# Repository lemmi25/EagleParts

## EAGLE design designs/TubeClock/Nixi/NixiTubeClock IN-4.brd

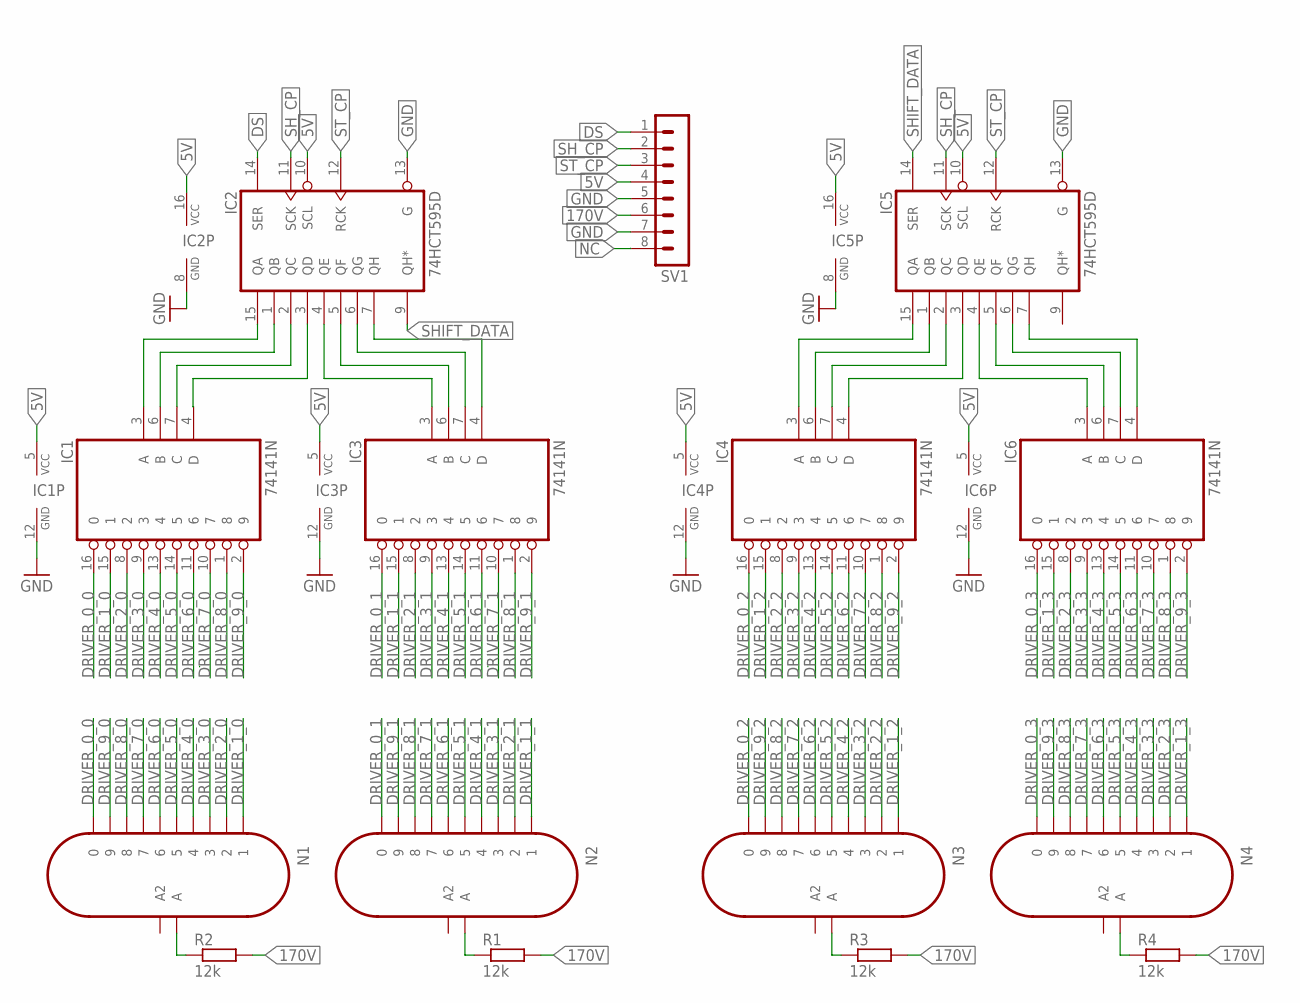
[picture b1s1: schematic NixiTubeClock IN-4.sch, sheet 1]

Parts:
IC1, IC3, IC4, IC6: 74141N; DIL16
IC2, IC5: 74HCT595D; SO16
N1, N2, N3, N4: IN-4; IN-18
R1, R2, R3, R4: 12k; R1206
SV1: MA08-1

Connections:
5V: IC1.5 (VCC), IC2.10 (SCL), IC2.16 (VCC), IC3.5 (VCC), IC4.5 (VCC), IC5.10 (SCL), IC5.16 (VCC), IC6.5 (VCC), SV1.4
170V: R1.2, R2.2, R3.2, R4.2, SV1.6
DRIVER_0_0: IC1.16 (0), N1.N/C2 (0)
DRIVER_0_1: IC3.16 (0), N2.N/C2 (0)
DRIVER_0_2: IC4.16 (0), N3.N/C2 (0)
DRIVER_0_3: IC6.16 (0), N4.N/C2 (0)
DRIVER_1_0: IC1.15 (1), N1.9 (1)
DRIVER_1_1: IC3.15 (1), N2.9 (1)
DRIVER_1_2: IC4.15 (1), N3.9 (1)
DRIVER_1_3: IC6.15 (1), N4.9 (1)
DRIVER_2_0: IC1.8 (2), N1.8 (2)
DRIVER_2_1: IC3.8 (2), N2.8 (2)
DRIVER_2_2: IC4.8 (2), N3.8 (2)
DRIVER_2_3: IC6.8 (2), N4.8 (2)
DRIVER_3_0: IC1.9 (3), N1.1 (3)
DRIVER_3_1: IC3.9 (3), N2.1 (3)
DRIVER_3_2: IC4.9 (3), N3.1 (3)
DRIVER_3_3: IC6.9 (3), N4.1 (3)
DRIVER_4_0: IC1.13 (4), N1.N/C (4)
DRIVER_4_1: IC3.13 (4), N2.N/C (4)
DRIVER_4_2: IC4.13 (4), N3.N/C (4)
DRIVER_4_3: IC6.13 (4), N4.N/C (4)
DRIVER_5_0: IC1.14 (5), N1.A2 (5)
DRIVER_5_1: IC3.14 (5), N2.A2 (5)
DRIVER_5_2: IC4.14 (5), N3.A2 (5)
DRIVER_5_3: IC6.14 (5), N4.A2 (5)
DRIVER_6_0: IC1.11 (6), N1.4 (6)
DRIVER_6_1: IC3.11 (6), N2.4 (6)
DRIVER_6_2: IC4.11 (6), N3.4 (6)
DRIVER_6_3: IC6.11 (6), N4.4 (6)
DRIVER_7_0: IC1.10 (7), N1.7
DRIVER_7_1: IC3.10 (7), N2.7
DRIVER_7_2: IC4.10 (7), N3.7
DRIVER_7_3: IC6.10 (7), N4.7
DRIVER_8_0: IC1.1 (8), N1.5 (8)
DRIVER_8_1: IC3.1 (8), N2.5 (8)
DRIVER_8_2: IC4.1 (8), N3.5 (8)
DRIVER_8_3: IC6.1 (8), N4.5 (8)
DRIVER_9_0: IC1.2 (9), N1.6 (9)
DRIVER_9_1: IC3.2 (9), N2.6 (9)
DRIVER_9_2: IC4.2 (9), N3.6 (9)
DRIVER_9_3: IC6.2 (9), N4.6 (9)
DS: IC2.14 (SER), SV1.1
GND: IC1.12 (GND), IC2.8 (GND), IC2.13 (G), IC3.12 (GND), IC4.12 (GND), IC5.8 (GND), IC5.13 (G), IC6.12 (GND), SV1.5, SV1.7
unnamed: IC4.4 (D), IC5.3 (QD)
unnamed: N2.0 (A), R1.1
unnamed: N3.0 (A), R3.1
unnamed: N4.0 (A), R4.1
unnamed: N1.0 (A), R2.1
unnamed: IC1.3 (A), IC2.15 (QA)
unnamed: IC1.6 (B), IC2.1 (QB)
unnamed: IC1.7 (C), IC2.2 (QC)
unnamed: IC1.4 (D), IC2.3 (QD)
unnamed: IC2.4 (QE), IC3.3 (A)
unnamed: IC2.5 (QF), IC3.6 (B)
unnamed: IC2.6 (QG), IC3.7 (C)
unnamed: IC2.7 (QH), IC3.4 (D)
unnamed: IC4.3 (A), IC5.15 (QA)
unnamed: IC4.6 (B), IC5.1 (QB)
unnamed: IC4.7 (C), IC5.2 (QC)
unnamed: IC5.4 (QE), IC6.3 (A)
unnamed: IC5.5 (QF), IC6.6 (B)
unnamed: IC5.6 (QG), IC6.7 (C)
unnamed: IC5.7 (QH), IC6.4 (D)
NC: SV1.8
SHIFT_DATA: IC2.9 (QH*), IC5.14 (SER)
SH_CP: IC2.11 (SCK), IC5.11 (SCK), SV1.2
ST_CP: IC2.12 (RCK), IC5.12 (RCK), SV1.3

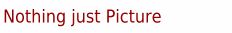
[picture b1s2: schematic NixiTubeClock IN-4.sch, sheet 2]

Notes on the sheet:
Nothing just Picture

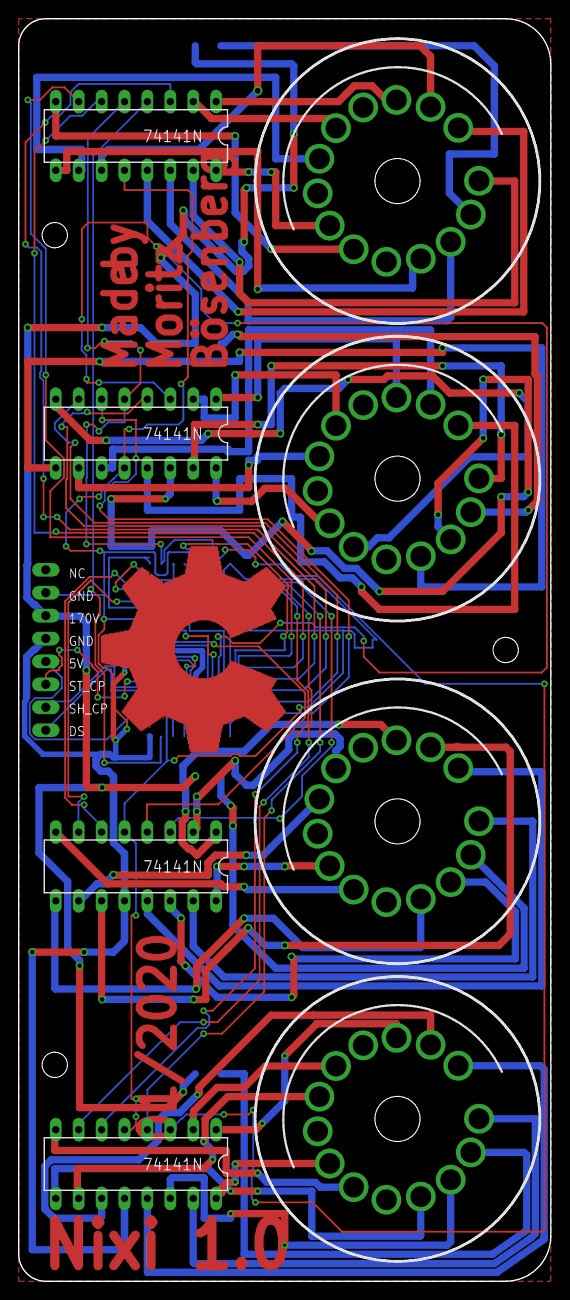
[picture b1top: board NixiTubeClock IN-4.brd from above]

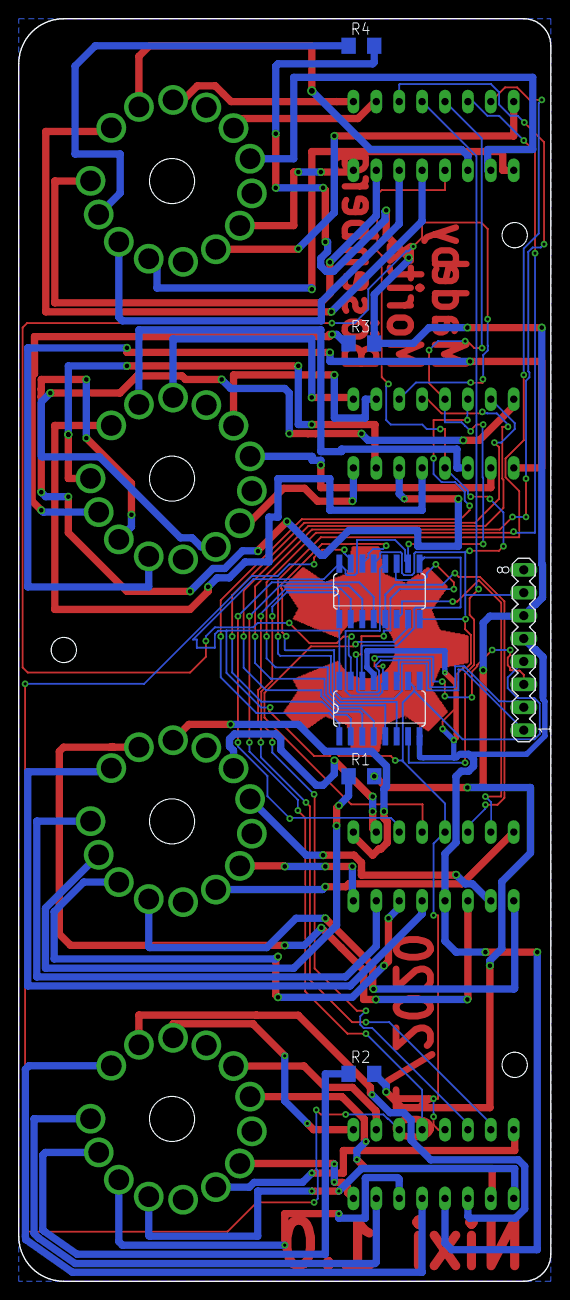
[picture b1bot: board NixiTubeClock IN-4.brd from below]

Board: 2 copper layers, 59.0 x 140.0 mm, 15 parts (7 on the bottom side), 67 nets.

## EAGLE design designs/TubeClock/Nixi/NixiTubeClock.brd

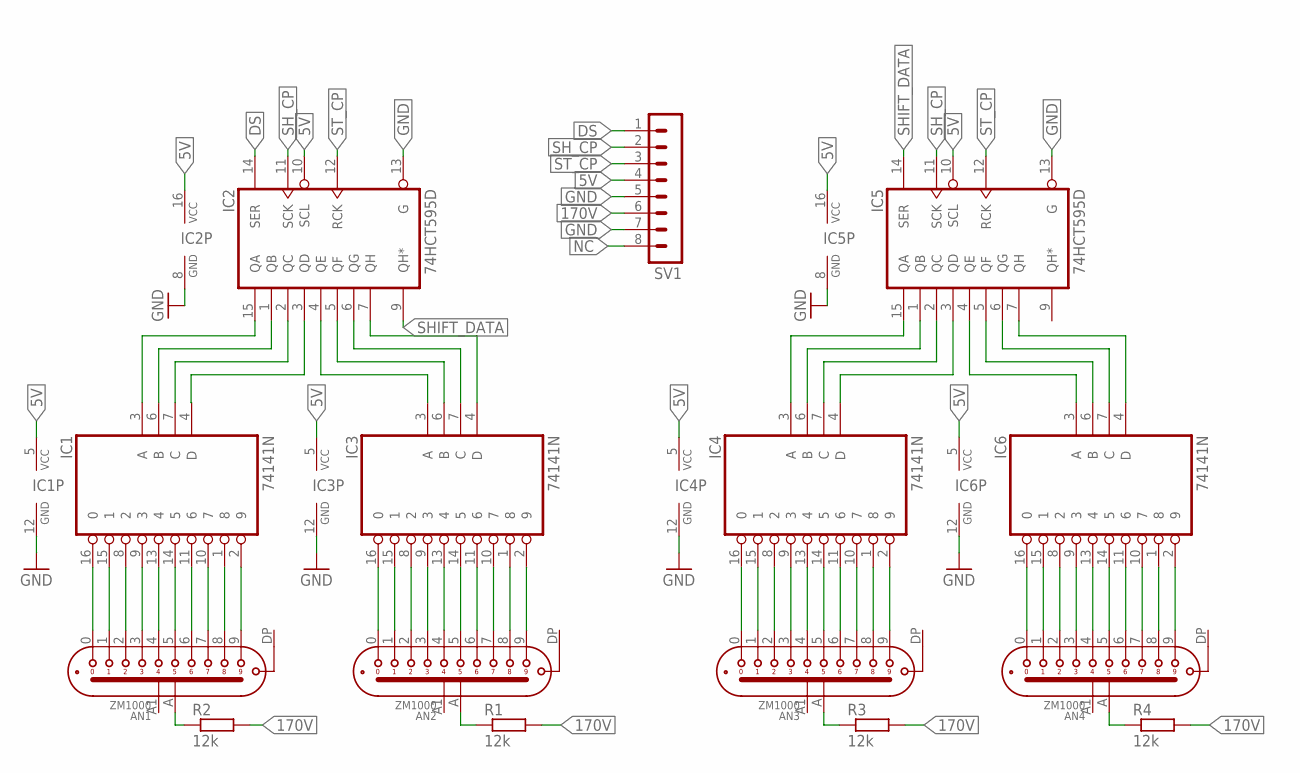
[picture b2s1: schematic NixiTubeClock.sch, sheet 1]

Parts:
AN1, AN2, AN3, AN4: ZM1000
IC1, IC3, IC4, IC6: 74141N; DIL16
IC2, IC5: 74HCT595D; SO16
R1, R2, R3, R4: 12k; R1206
SV1: MA08-1

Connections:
5V: IC1.5 (VCC), IC2.10 (SCL), IC2.16 (VCC), IC3.5 (VCC), IC4.5 (VCC), IC5.10 (SCL), IC5.16 (VCC), IC6.5 (VCC), SV1.4
170V: R1.2, R2.2, R3.2, R4.2, SV1.6
DS: IC2.14 (SER), SV1.1
GND: IC1.12 (GND), IC2.8 (GND), IC2.13 (G), IC3.12 (GND), IC4.12 (GND), IC5.8 (GND), IC5.13 (G), IC6.12 (GND), SV1.5, SV1.7
unnamed: IC4.4 (D), IC5.3 (QD)
unnamed: AN1.0, IC1.16 (0)
unnamed: AN1.1, IC1.15 (1)
unnamed: AN1.2, IC1.8 (2)
unnamed: AN1.3, IC1.9 (3)
unnamed: AN1.4, IC1.13 (4)
unnamed: AN1.5, IC1.14 (5)
unnamed: AN1.6, IC1.11 (6)
unnamed: AN1.7, IC1.10 (7)
unnamed: AN1.8, IC1.1 (8)
unnamed: AN1.9, IC1.2 (9)
unnamed: AN2.0, IC3.16 (0)
unnamed: AN2.1, IC3.15 (1)
unnamed: AN2.2, IC3.8 (2)
unnamed: AN2.3, IC3.9 (3)
unnamed: AN2.4, IC3.13 (4)
unnamed: AN2.5, IC3.14 (5)
unnamed: AN2.6, IC3.11 (6)
unnamed: AN2.7, IC3.10 (7)
unnamed: AN2.8, IC3.1 (8)
unnamed: AN2.9, IC3.2 (9)
unnamed: AN3.0, IC4.16 (0)
unnamed: AN3.1, IC4.15 (1)
unnamed: AN3.2, IC4.8 (2)
unnamed: AN3.3, IC4.9 (3)
unnamed: AN3.4, IC4.13 (4)
unnamed: AN3.5, IC4.14 (5)
unnamed: AN3.6, IC4.11 (6)
unnamed: AN3.7, IC4.10 (7)
unnamed: AN3.8, IC4.1 (8)
unnamed: AN3.9, IC4.2 (9)
unnamed: AN4.0, IC6.16 (0)
unnamed: AN4.1, IC6.15 (1)
unnamed: AN4.2, IC6.8 (2)
unnamed: AN4.3, IC6.9 (3)
unnamed: AN4.4, IC6.13 (4)
unnamed: AN4.5, IC6.14 (5)
unnamed: AN4.6, IC6.11 (6)
unnamed: AN4.7, IC6.10 (7)
unnamed: AN4.8, IC6.1 (8)
unnamed: AN4.9, IC6.2 (9)
unnamed: AN1.A (A1), R2.1
unnamed: AN2.A (A1), R1.1
unnamed: AN3.A (A1), R3.1
unnamed: AN4.A (A1), R4.1
unnamed: IC1.3 (A), IC2.15 (QA)
unnamed: IC1.6 (B), IC2.1 (QB)
unnamed: IC1.7 (C), IC2.2 (QC)
unnamed: IC1.4 (D), IC2.3 (QD)
unnamed: IC2.4 (QE), IC3.3 (A)
unnamed: IC2.5 (QF), IC3.6 (B)
unnamed: IC2.6 (QG), IC3.7 (C)
unnamed: IC2.7 (QH), IC3.4 (D)
unnamed: IC4.3 (A), IC5.15 (QA)
unnamed: IC4.6 (B), IC5.1 (QB)
unnamed: IC4.7 (C), IC5.2 (QC)
unnamed: IC5.4 (QE), IC6.3 (A)
unnamed: IC5.5 (QF), IC6.6 (B)
unnamed: IC5.6 (QG), IC6.7 (C)
unnamed: IC5.7 (QH), IC6.4 (D)
NC: SV1.8
SHIFT_DATA: IC2.9 (QH*), IC5.14 (SER)
SH_CP: IC2.11 (SCK), IC5.11 (SCK), SV1.2
ST_CP: IC2.12 (RCK), IC5.12 (RCK), SV1.3

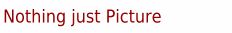
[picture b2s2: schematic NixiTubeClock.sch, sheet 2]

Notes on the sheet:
Nothing just Picture

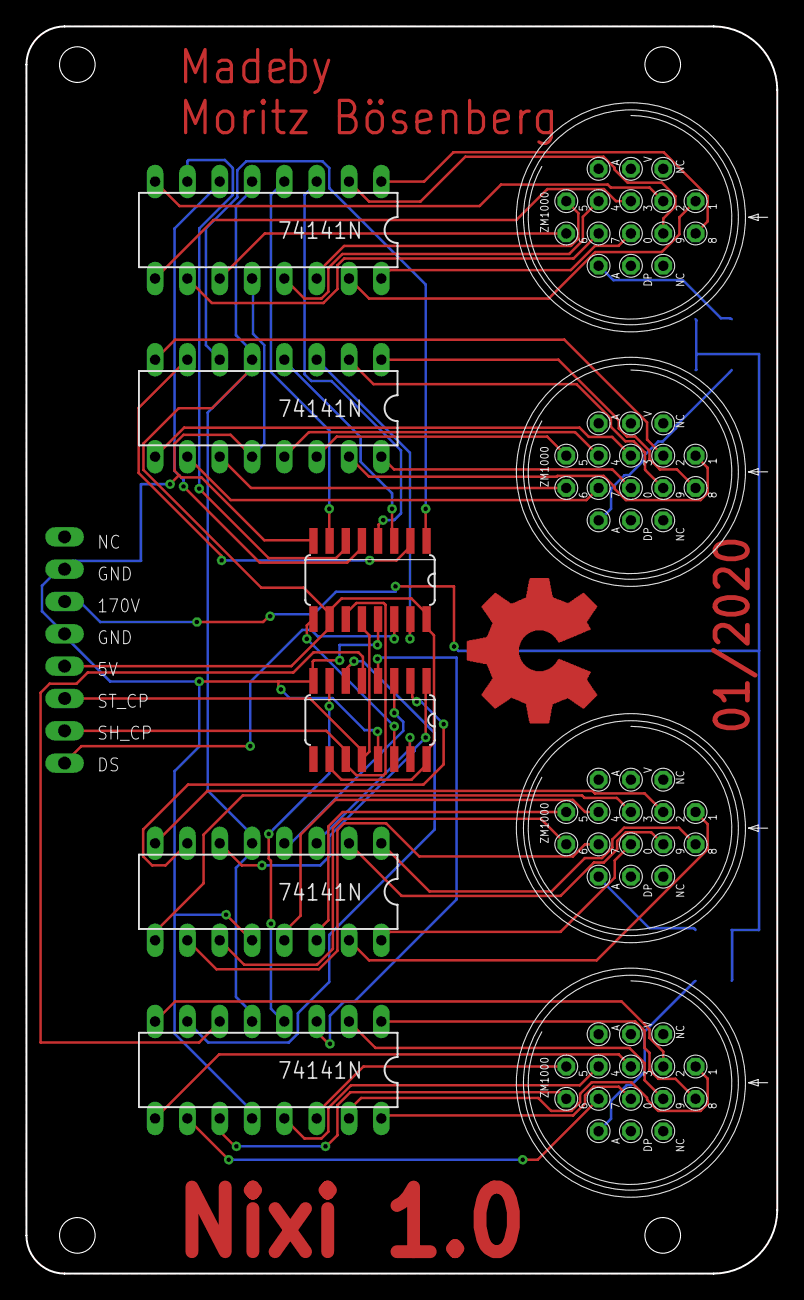
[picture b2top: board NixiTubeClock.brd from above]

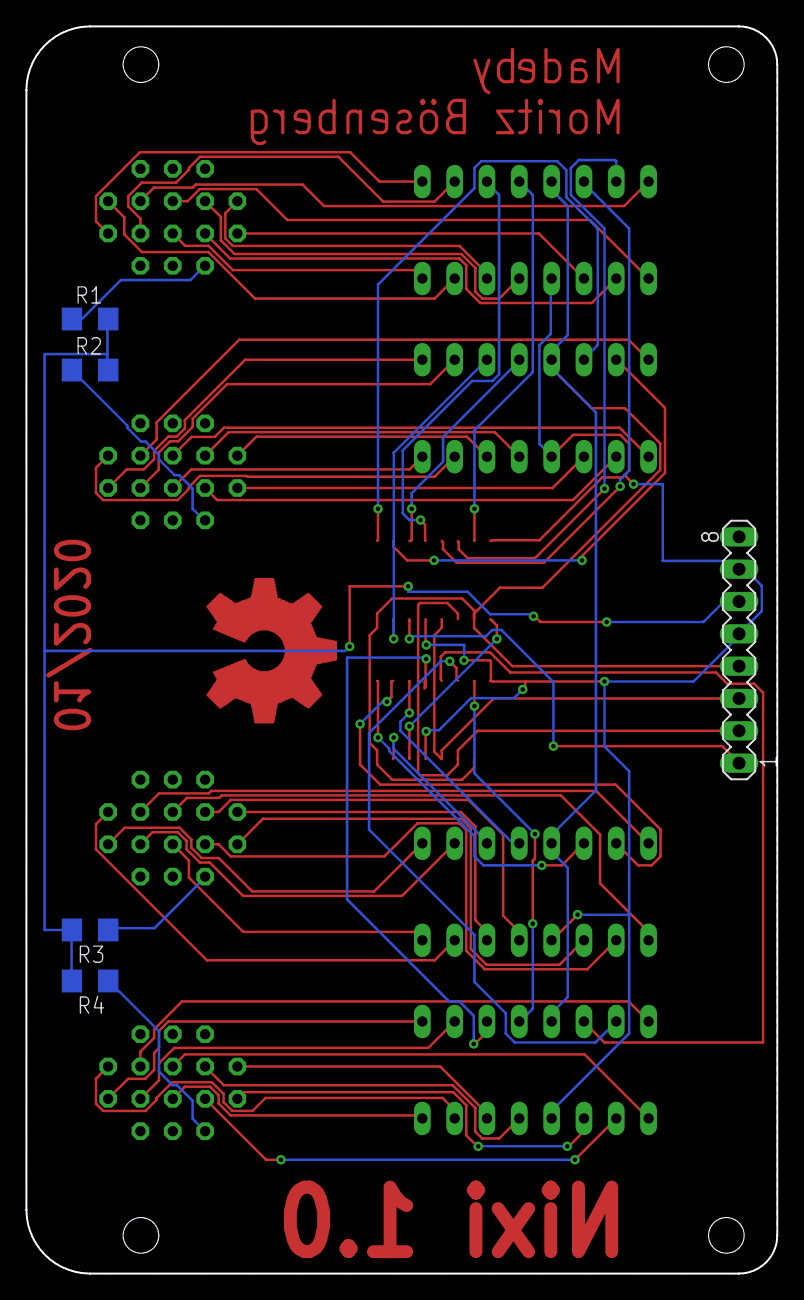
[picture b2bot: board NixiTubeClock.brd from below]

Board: 2 copper layers, 59.0 x 98.0 mm, 15 parts (5 on the bottom side), 67 nets.

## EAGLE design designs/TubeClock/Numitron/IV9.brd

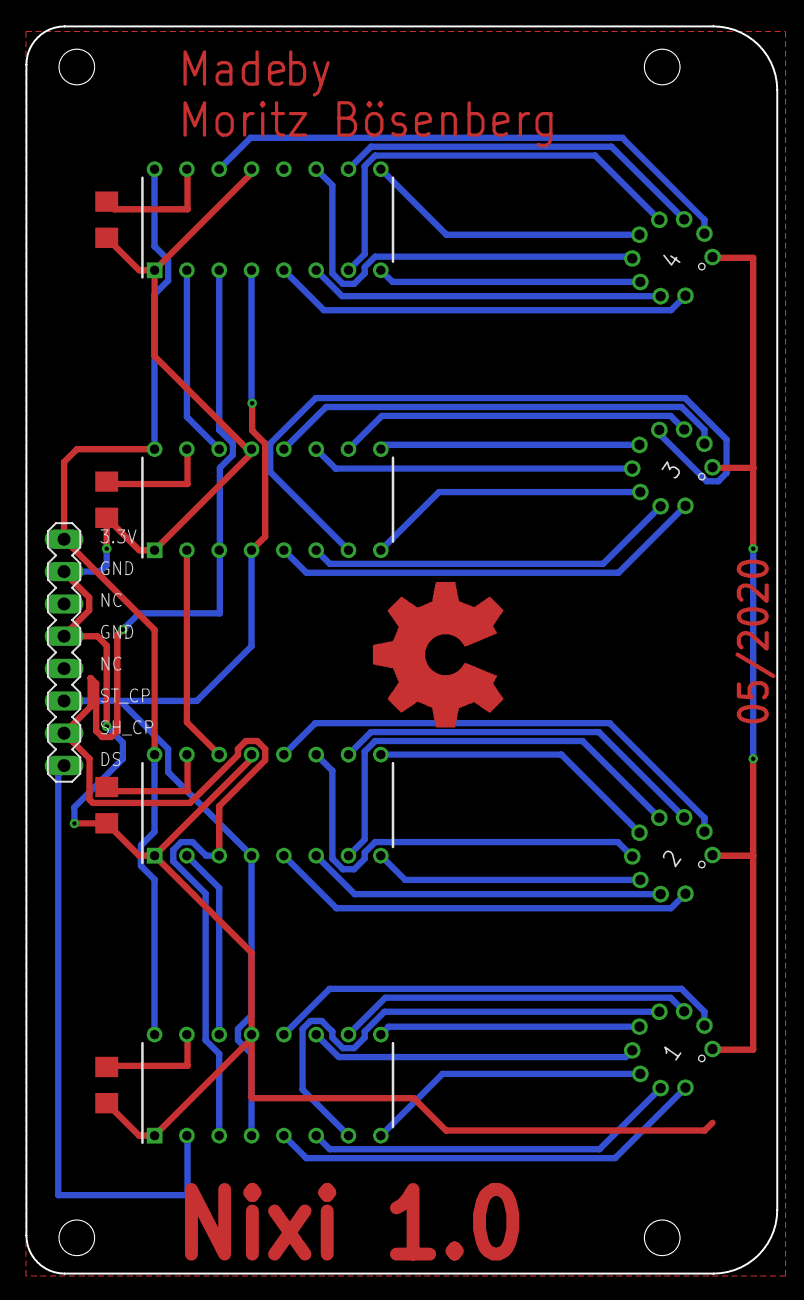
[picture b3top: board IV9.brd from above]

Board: 2 copper layers, 59.0 x 98.0 mm, 13 parts (0 on the bottom side), 44 nets.

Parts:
1, 2, 3, 4: IV-9
IC1, IC2, IC3, IC4: TLC5916IN; DIP794W53P254L1930H508Q16N
R1, R2, R3, R4: 1K; R1206
SV2: MA08-1

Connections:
3.3V: 1.1, 2.1, 3.1, 4.1, IC1.16, IC2.16, IC3.16, IC4.16, SV2.8
A_1: 1.5, IC1.9
A_2: 2.5, IC2.9
A_3: 3.5, IC3.9
A_4: 4.5, IC4.9
B_1: 1.3, IC1.10
B_2: 2.3, IC2.10
B_3: 3.3, IC3.10
B_4: 4.3, IC4.10
C_1: 1.4, IC1.7
C_2: 2.4, IC2.7
C_3: 3.4, IC3.7
C_4: 4.4, IC4.7
DEC_1: 1.2, IC1.12
DEC_2: 2.2, IC2.12
DEC_3: 3.2, IC3.12
DEC_4: 4.2, IC4.14
DS: IC1.2, SV2.1
D_1: 1.8, IC1.6
D_2: 2.8, IC2.6
D_3: 3.8, IC3.6
D_4: 4.8, IC4.6
E_1: 1.9, IC1.5
E_2: 2.9, IC2.5
E_3: 3.9, IC3.5
E_4: 4.9, IC4.5
F_1: 1.6, IC1.11
F_2: 2.6, IC2.11
F_3: 3.6, IC3.11
F_4: 4.6, IC4.11
GND: IC1.1, IC1.13, IC2.1, IC2.13, IC3.1, IC3.13, IC4.1, IC4.13, R1.1, R2.1, R3.1, R4.1, SV2.5, SV2.7
G_1: 1.7, IC1.8
G_2: 2.7, IC2.8
G_3: 3.7, IC3.8
G_4: 4.7, IC4.8
unnamed: IC1.14, IC2.2
unnamed: IC2.14, IC3.2
unnamed: IC3.14, IC4.2
R-EXT1: IC1.15, R1.2
R-EXT2: IC2.15, R2.2
R-EXT3: IC3.15, R3.2
R-EXT4: IC4.15, R4.2
SH_CP: IC1.3, IC2.3, IC3.3, IC4.3, SV2.2
ST_CP: IC1.4, IC2.4, IC3.4, IC4.4, SV2.3

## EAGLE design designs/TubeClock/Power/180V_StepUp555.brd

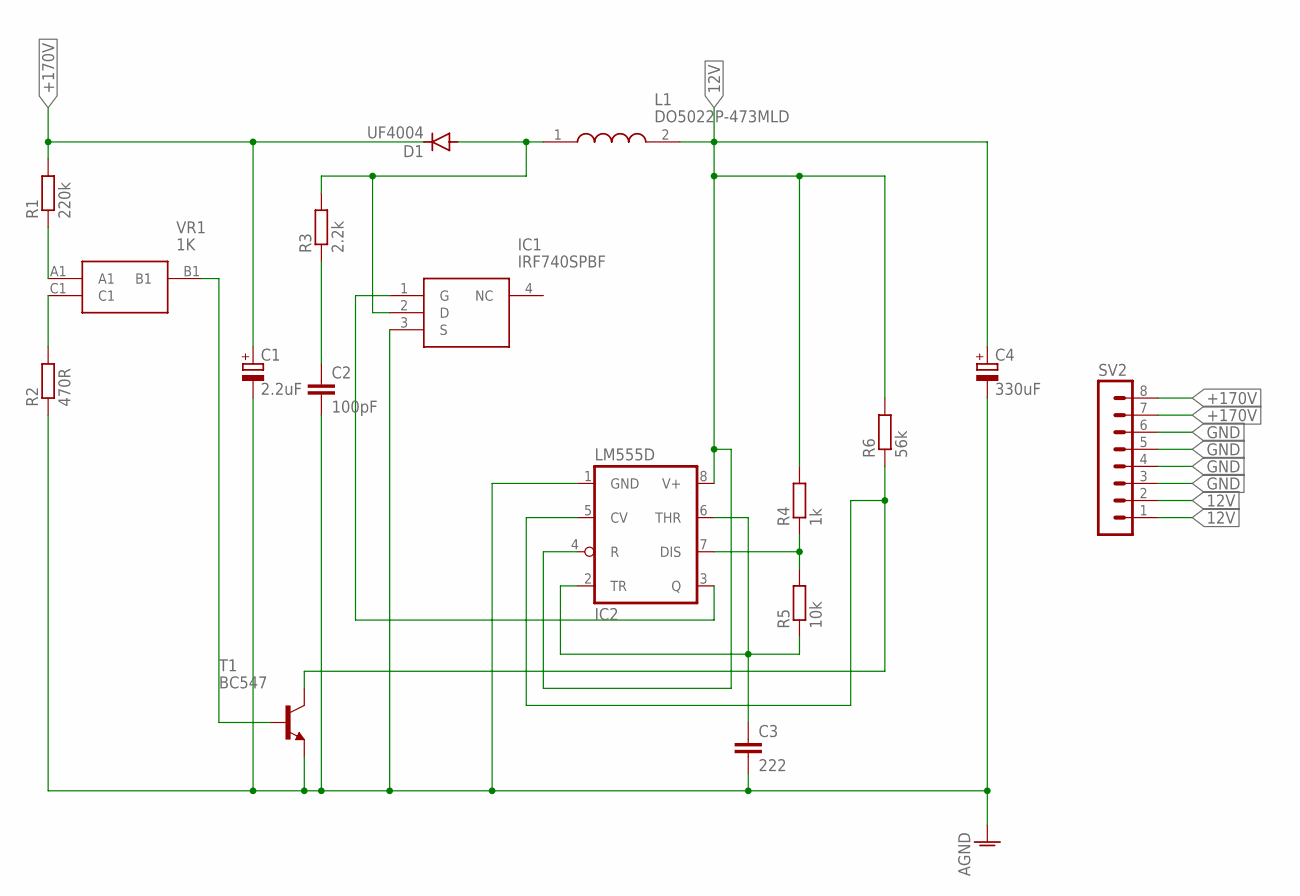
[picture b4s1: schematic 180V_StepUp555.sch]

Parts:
C1: 2.2uF; E2,5-6
C2: 100pF; C050-024X044
C3: 222; C050-024X044
C4: 330uF; E2,5-6
D1: UF4004; DO41-7.6
IC1: IRF740SPBF; TO254P1524X483-4N
IC2: LM555D; SO08
L1: DO5022P-473MLD; DO5022P473MLD
R1: 220k; 0207/10
R2: 470R; 0207/10
R3: 2.2k; 0207/10
R4: 1k; 0207/10
R5: 10k; 0207/10
R6: 56k; 0207/10
SV2: MA08-1
T1: BC547; TO92
VR1: 1K; EVM3YSX50B14

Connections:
12V: C4.+, IC2.4 (R), IC2.8 (V+), L1.2, R4.2, R6.2, SV2.1, SV2.2
+170V: C1.+, D1.C, R1.2, SV2.7, SV2.8
GND: C1.-, C2.2, C3.2, C4.-, IC1.3 (S), IC2.1 (GND), R2.1, SV2.3, SV2.4, SV2.5, SV2.6, T1.1 (E)
unnamed: R2.2, VR1.C1
unnamed: R1.1, VR1.A1
unnamed: T1.2 (B), VR1.B1
unnamed: D1.A, IC1.2 (D), L1.1, R3.2
unnamed: IC2.5 (CV), R6.1, T1.3 (C)
unnamed: C2.1, R3.1
unnamed: C3.1, IC2.2 (TR), IC2.6 (THR), R5.1
unnamed: IC2.7 (DIS), R4.1, R5.2
unnamed: IC1.1 (G), IC2.3 (Q)

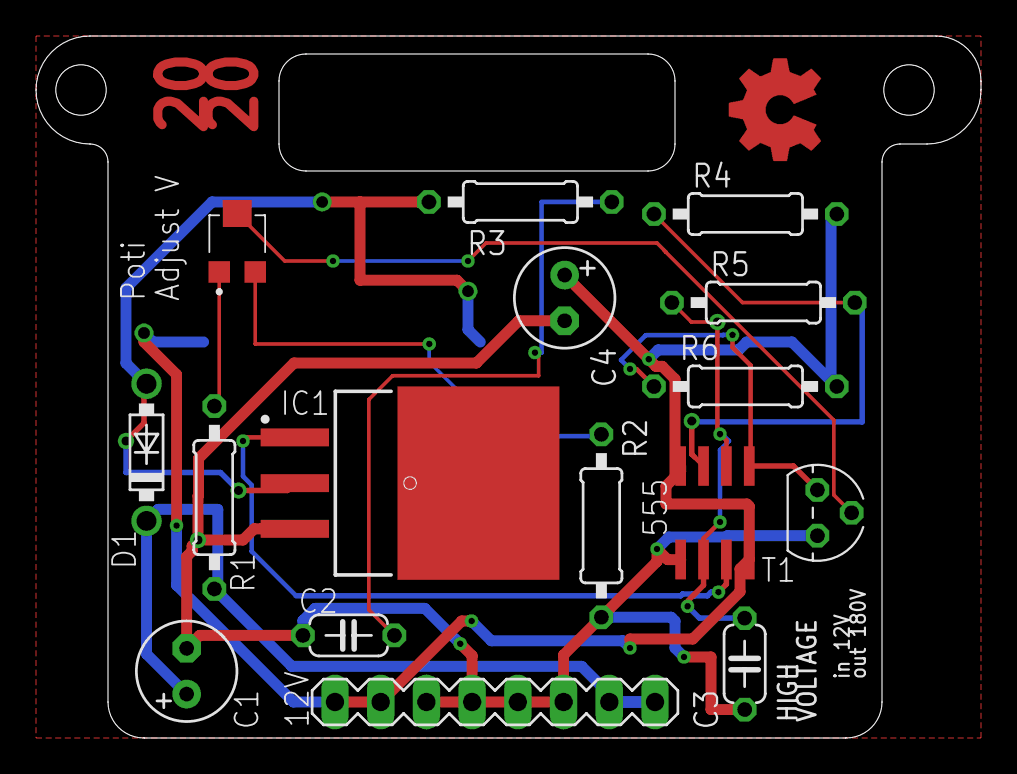
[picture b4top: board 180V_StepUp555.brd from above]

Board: 2 copper layers, 52.5 x 39.0 mm, 17 parts (1 on the bottom side), 12 nets.

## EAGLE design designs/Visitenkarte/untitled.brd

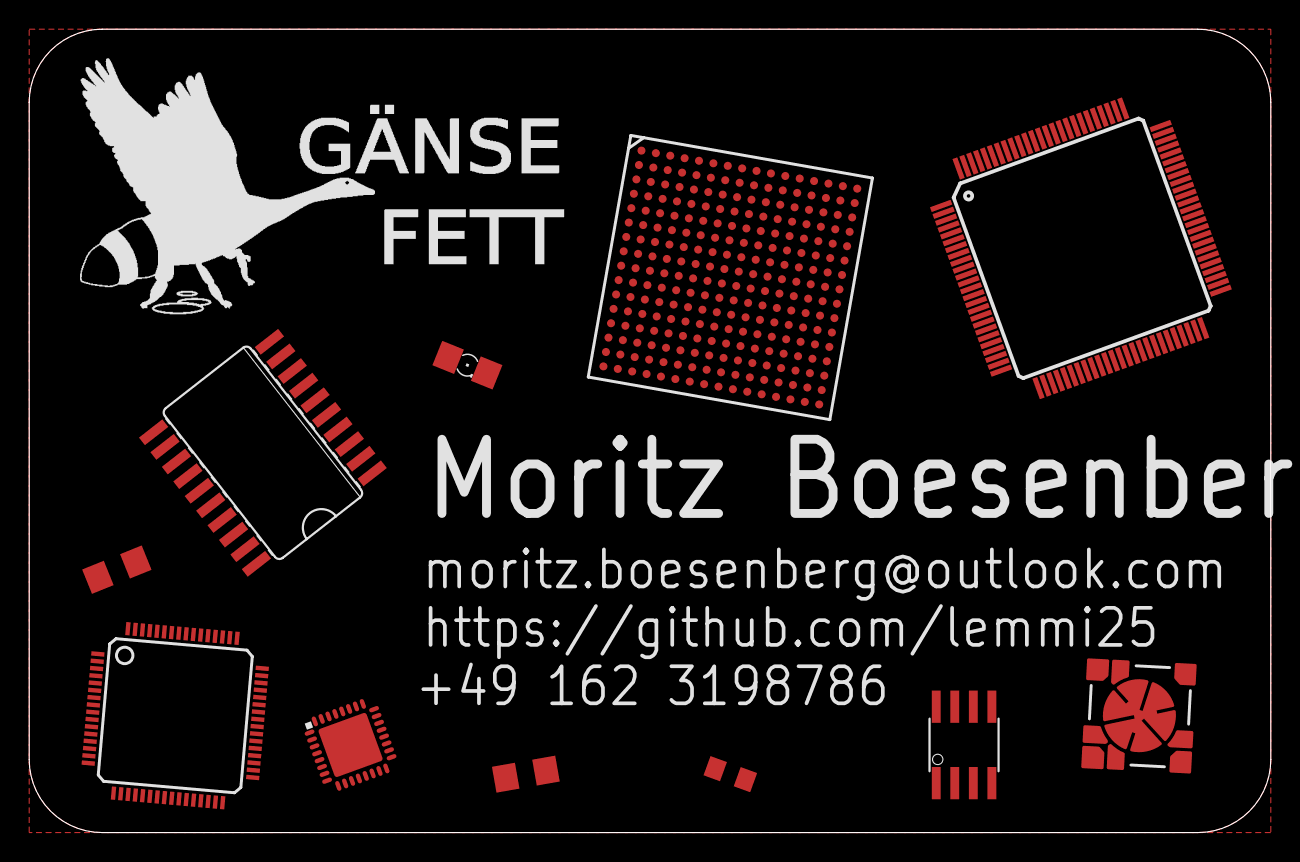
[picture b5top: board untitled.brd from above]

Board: 2 copper layers, 85.0 x 55.0 mm, 11 parts (0 on the bottom side), 6 nets, no tracks yet.

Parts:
C1, C2: C1206
IC1: XMEGA128A1; TQFP100
IC2: STM8S105K; UFQFPN32
IC3: 74AC11034D; SO20W
IC4: INA117U; SO08
IC5: EP2C20F256; FBGA256
IC6: ADAV804; LQFP-ST-64-2
LED1: LZ4-40U600
LED2: 1206
R1: VARISTORCN0805; CT/CN0805

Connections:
AGND: IC6.3, IC6.54, IC6.56, IC6.58, IC6.62
AVDD: IC6.4, IC6.53
DGND: IC6.16, IC6.33
DVDD: IC6.15, IC6.34
GND: IC1.3, IC3.4, IC3.5, IC3.6, IC3.7, IC5.A1, IC5.A16, IC5.B2, IC5.B15, IC5.C8, IC5.C9, IC5.D5, IC5.D12, IC5.E6, IC5.E8, IC5.E9, IC5.E11, IC5.F5, IC5.F7, IC5.F8, IC5.F12, IC5.G6, IC5.G8, IC5.G10, IC5.H3, IC5.H6, IC5.H8, IC5.H9, IC5.H14, IC5.J3, IC5.J8, IC5.J9, IC5.J11, IC5.J14, IC5.K7, IC5.K9, IC5.K11, IC5.L5, IC5.L9, IC5.L10, IC5.L12, IC5.M6, IC5.M8, IC5.M9, IC5.M11, IC5.N5, IC5.N12, IC5.P8, IC5.P9, IC5.R2, IC5.R15, IC5.T1, IC5.T16
VCC: IC1.14, IC3.15, IC3.16, IC5.A2, IC5.A15, IC5.B1, IC5.B16, IC5.C7, IC5.C10, IC5.E5, IC5.E7, IC5.E10, IC5.E12, IC5.F6, IC5.F9, IC5.F10, IC5.F11, IC5.G3, IC5.G7, IC5.G9, IC5.G11, IC5.G14, IC5.H7, IC5.H10, IC5.H11, IC5.J6, IC5.J7, IC5.J10, IC5.K3, IC5.K6, IC5.K8, IC5.K10, IC5.K14, IC5.L6, IC5.L7, IC5.L8, IC5.L11, IC5.M5, IC5.M7, IC5.M10, IC5.M12, IC5.P7, IC5.P10, IC5.R1, IC5.R16, IC5.T2, IC5.T15
